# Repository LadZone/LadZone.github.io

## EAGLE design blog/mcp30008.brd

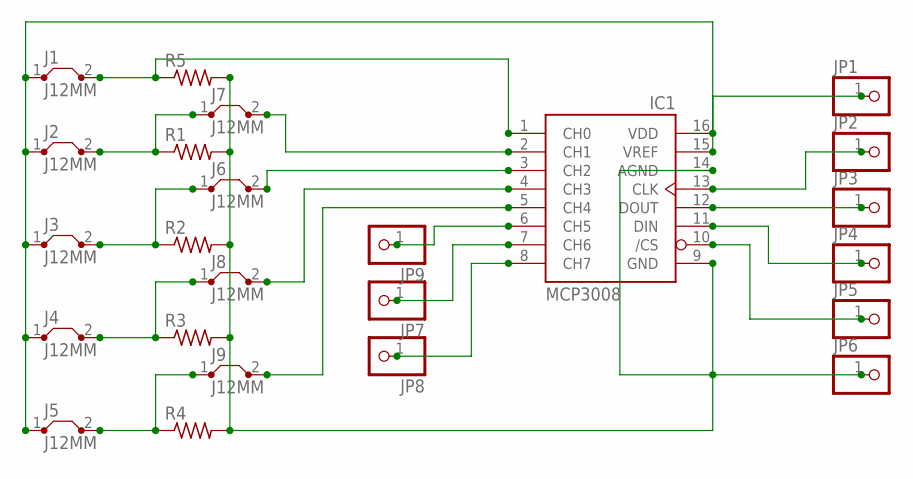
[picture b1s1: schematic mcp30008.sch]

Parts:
IC1: MCP3008; DIL16
J1, J2, J3, J4, J5, J6, J7, J8, J9: J12MM; 12
JP1, JP2, JP3, JP4, JP5, JP6, JP7, JP8, JP9: PINHD-1X1; 1X01
R1, R2, R3, R4, R5: R-US_0207/15; 0207/15

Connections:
unnamed: IC1.6 (CH5), JP9.1
unnamed: IC1.1 (CH0), J1.2, R5.1
unnamed: IC1.13 (CLK), JP2.1
unnamed: IC1.12 (DOUT), JP3.1
unnamed: IC1.11 (DIN), JP4.1
unnamed: IC1.10 (/CS), JP5.1
unnamed: IC1.3 (CH2), J6.2
unnamed: IC1.4 (CH3), J8.2
unnamed: IC1.8 (CH7), JP8.1
unnamed: IC1.15 (VREF), IC1.16 (VDD), J1.1, J2.1, J3.1, J4.1, J5.1, JP1.1
unnamed: J5.2, J9.1, R4.1
unnamed: IC1.5 (CH4), J9.2
unnamed: J4.2, J8.1, R3.1
unnamed: IC1.2 (CH1), J7.2
unnamed: J2.2, J7.1, R1.1
unnamed: J3.2, J6.1, R2.1
unnamed: IC1.9 (GND), IC1.14 (AGND), JP6.1, R1.2, R2.2, R3.2, R4.2, R5.2
unnamed: IC1.7 (CH6), JP7.1

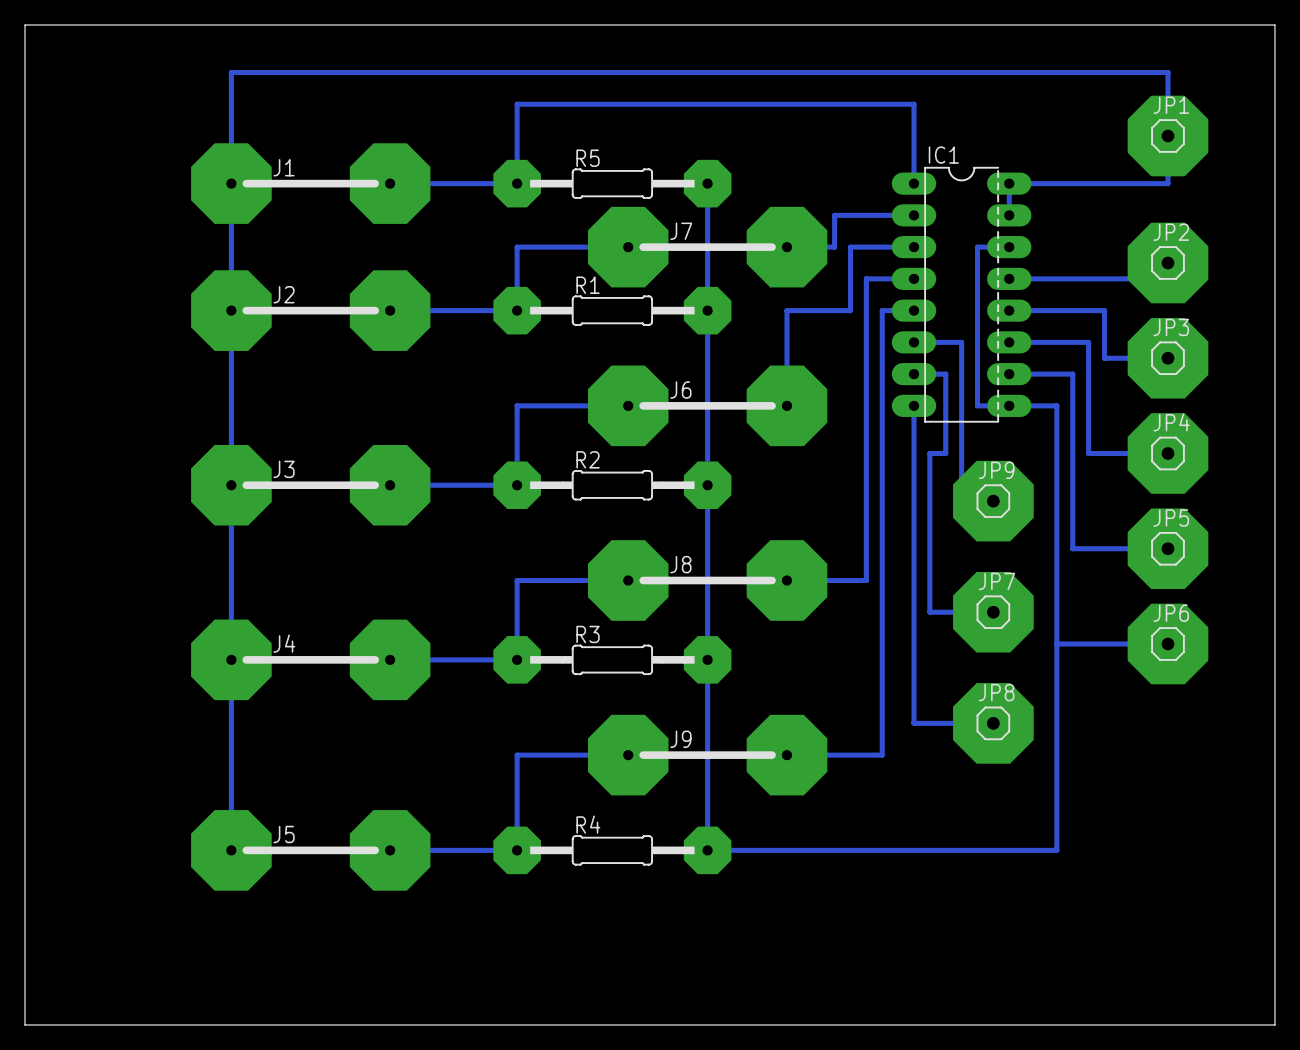
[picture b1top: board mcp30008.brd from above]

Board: 2 copper layers, 100.0 x 80.0 mm, 24 parts (0 on the bottom side), 18 nets.

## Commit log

2016-09-08 LED blink
    LED rPi3
2016-09-08 led pic
    led pic
2016-09-08 webpage
2016-09-08 folder for web
2016-09-12 led1
2016-10-11 menu update
2016-10-12 week 6
2016-10-19 week 7 update
2016-10-19 week 4
2016-10-26 card
2016-10-26 work
2016-10-26 pic photo
2016-11-07 meanu
2016-11-07 VIDEO
2016-11-16 open house
2016-11-25 mager update
2016-11-25 mcp3008
2016-11-25 code
2016-11-25 update code
2016-11-25 oktest
2016-11-25 final
2016-11-30 week 13
2016-12-13 week14
